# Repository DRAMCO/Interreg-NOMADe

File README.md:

# Interreg NOMADe
 Documentation about the Interreg NOMADe project

## Firmware
 This map contains the c/c++ code for both the DCU (Data Capturing Unit) and the motion sensor module
 
## Hardware
 Here you can find the Eagle schematics for the DCU and the sensor module

## Drawings
 Contains the 3D part files and STL files. 
 
 ## How to cite
```LaTex
@Misc{Interreg-NOMADe,
  author =   {J. Van Mulders},
  title =    {{Interreg-NOMADe}},
  howpublished  = "\url{https://github.com/DRAMCO/Interreg-NOMAD}",
  doi = {10.5281/zenodo.4005810}
}
```

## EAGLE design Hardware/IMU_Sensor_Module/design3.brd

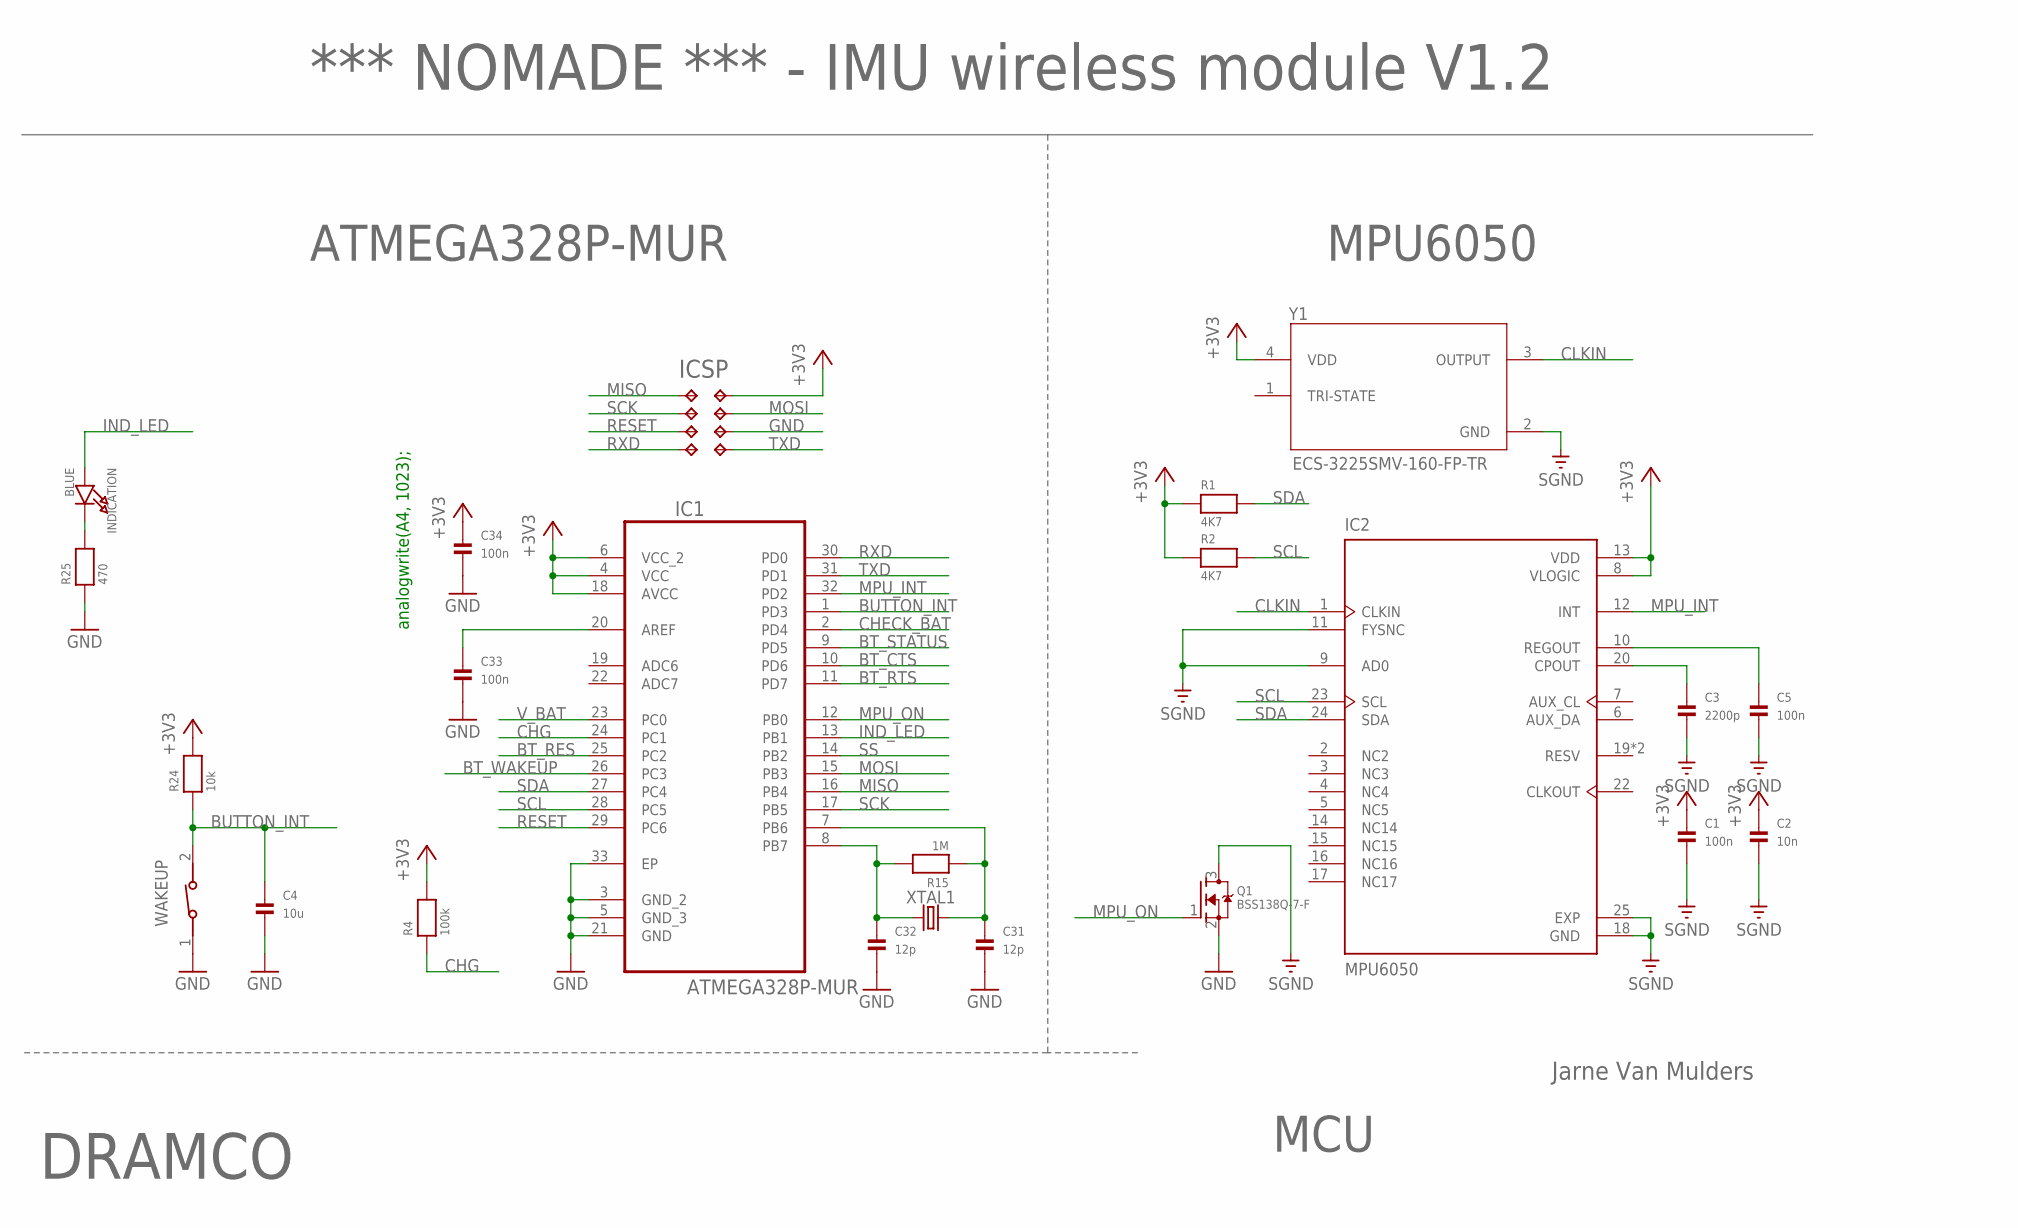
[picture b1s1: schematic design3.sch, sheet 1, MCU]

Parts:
3V3: TPTP16R; TP16R
C1, C5, C33, C34: 100n; 0603
C2: 10n; 0603
C3: 2200p; 0603
C4: 10u; 0805
C31, C32: 12p; 0603
GND: TPTP16R; TP16R
IC1: ATMEGA328P-MUR; QFN50P500X500X100-33N
IC2: MPU6050; IC_MPU6050
INDICATION: BLUE; CHIPLED_0805
MISO: TPTP16R; TP16R
MOSI: TPTP16R; TP16R
Q1: BSS138Q-7-F; SOT23-WIDE
R1, R2: 4K7; 0603
R4: 100k; 0603
R15: 1M; 0603
R24: 10k; 0603
R25: 470; 0603
RES: TPTP16R; TP16R
RXD: TPTP16R; TP16R
TP9: TPTP16R; TP16R
TXD: TPTP16R; TP16R
WAKEUP: 434111043826
XTAL1: CRYSTALSMD-3.2X2.5; CRYSTAL-SMD-3.2X2.5MM
Y1: ECS-3225SMV-160-FP-TR; OSC_ECS-2333-160-BN-TR

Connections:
+3V3: 3V3.TP, C1.1, C2.1, C34.1, IC1.4 (VCC), IC1.6 (VCC_2), IC1.18 (AVCC), IC2.8 (VLOGIC), IC2.13 (VDD), R1.1, R2.1, R4.2, R24.2, Y1.4 (VDD); also elsewhere on the board
BT_CTS: IC1.10 (PD6); also elsewhere on the board
BT_RES: IC1.25 (PC2); also elsewhere on the board
BT_RTS: IC1.11 (PD7); also elsewhere on the board
BT_STATUS: IC1.9 (PD5); also elsewhere on the board
BT_WAKEUP: IC1.26 (PC3); also elsewhere on the board
BUTTON_INT: C4.1, IC1.1 (PD3), R24.1, WAKEUP.2
CHECK_BAT: IC1.2 (PD4); also elsewhere on the board
CHG: IC1.24 (PC1), R4.1; also elsewhere on the board
CLKIN: IC2.1 (CLKIN), Y1.3 (OUTPUT)
GND: C4.2, C31.2, C32.2, C33.2, C34.2, GND.TP, IC1.3 (GND_2), IC1.5 (GND_3), IC1.21 (GND), IC1.33 (EP), Q1.2 (S), R25.1, WAKEUP.1; also elsewhere on the board
IND: INDICATION.C, R25.2
IND_LED: IC1.13 (PB1), INDICATION.A
MISO: IC1.16 (PB4), MISO.TP
MOSI: IC1.15 (PB3), MOSI.TP
MPU_INT: IC1.32 (PD2), IC2.12 (INT)
MPU_ON: IC1.12 (PB0), Q1.1 (G)
unnamed: C3.1, IC2.20 (CPOUT)
unnamed: C5.1, IC2.10 (REGOUT)
unnamed: C31.1, IC1.7 (PB6), R15.1, XTAL1.3 (2)
unnamed: C32.1, IC1.8 (PB7), R15.2, XTAL1.1
unnamed: C33.1, IC1.20 (AREF)
RESET: IC1.29 (PC6), RES.TP
RXD: IC1.30 (PD0), RXD.TP; also elsewhere on the board
SCK: IC1.17 (PB5), TP9.TP
SCL: IC1.28 (PC5), IC2.23 (SCL), R2.2
SDA: IC1.27 (PC4), IC2.24 (SDA), R1.2
SGND: C1.2, C2.2, C3.2, C5.2, IC2.9 (AD0), IC2.11 (FYSNC), IC2.18 (GND), IC2.25 (EXP), Q1.3 (D), Y1.2 (GND)
SS: IC1.14 (PB2)
TXD: IC1.31 (PD1), TXD.TP; also elsewhere on the board
V_BAT: IC1.23 (PC0); also elsewhere on the board

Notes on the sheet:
ATMEGA328P-MUR
*** NOMADE *** - IMU wireless module V1.2
MCU
Jarne Van Mulders
DRAMCO
ICSP
analogwrite(A4, 1023);
MPU6050

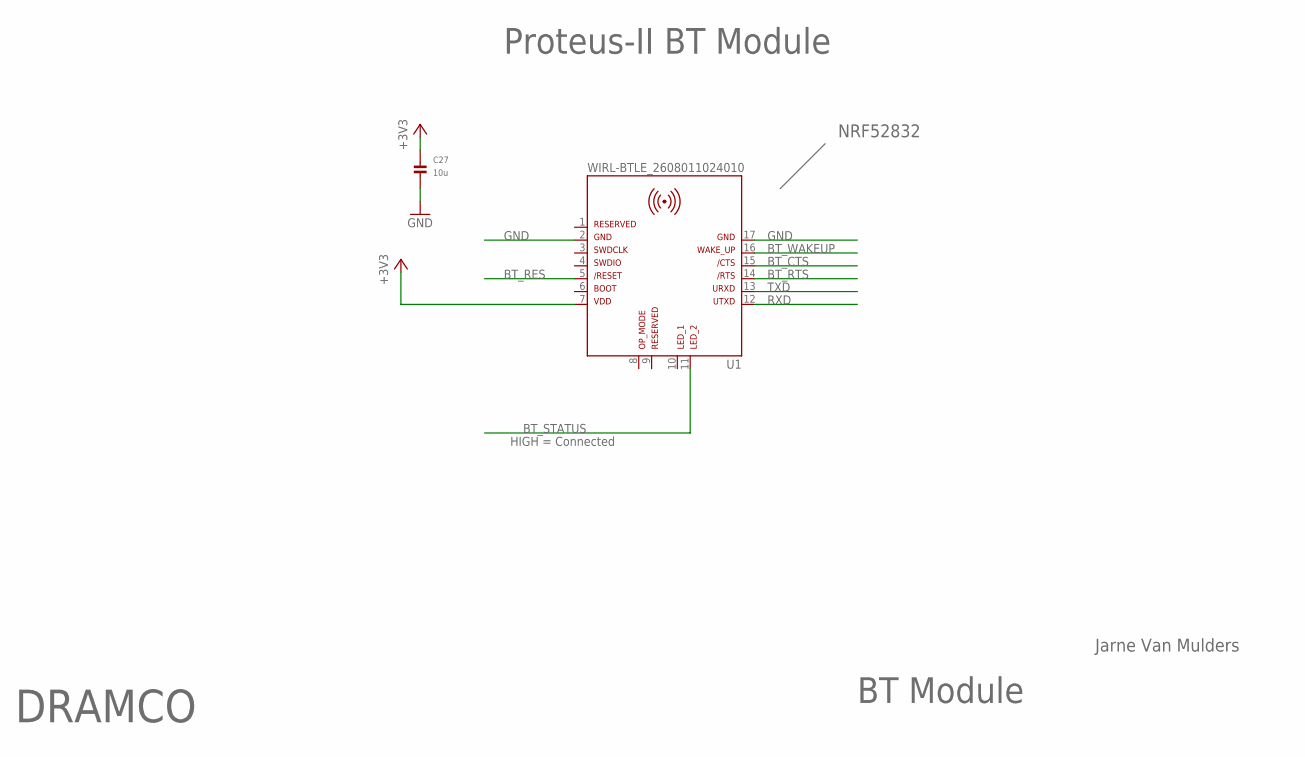
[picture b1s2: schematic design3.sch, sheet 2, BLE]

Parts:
C27: 10u; 0805
U1: WIRL-BTLE_2608011024010

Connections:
+3V3: C27.1, U1.7; also elsewhere on the board
BT_CTS: U1.15; also elsewhere on the board
BT_RES: U1.5; also elsewhere on the board
BT_RTS: U1.14; also elsewhere on the board
BT_STATUS: U1.11; also elsewhere on the board
BT_WAKEUP: U1.16; also elsewhere on the board
GND: C27.2, U1.2, U1.17; also elsewhere on the board
RXD: U1.12; also elsewhere on the board
TXD: U1.13; also elsewhere on the board

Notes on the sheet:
HIGH = Connected
BT Module
Jarne Van Mulders
DRAMCO
Proteus-II BT Module
NRF52832

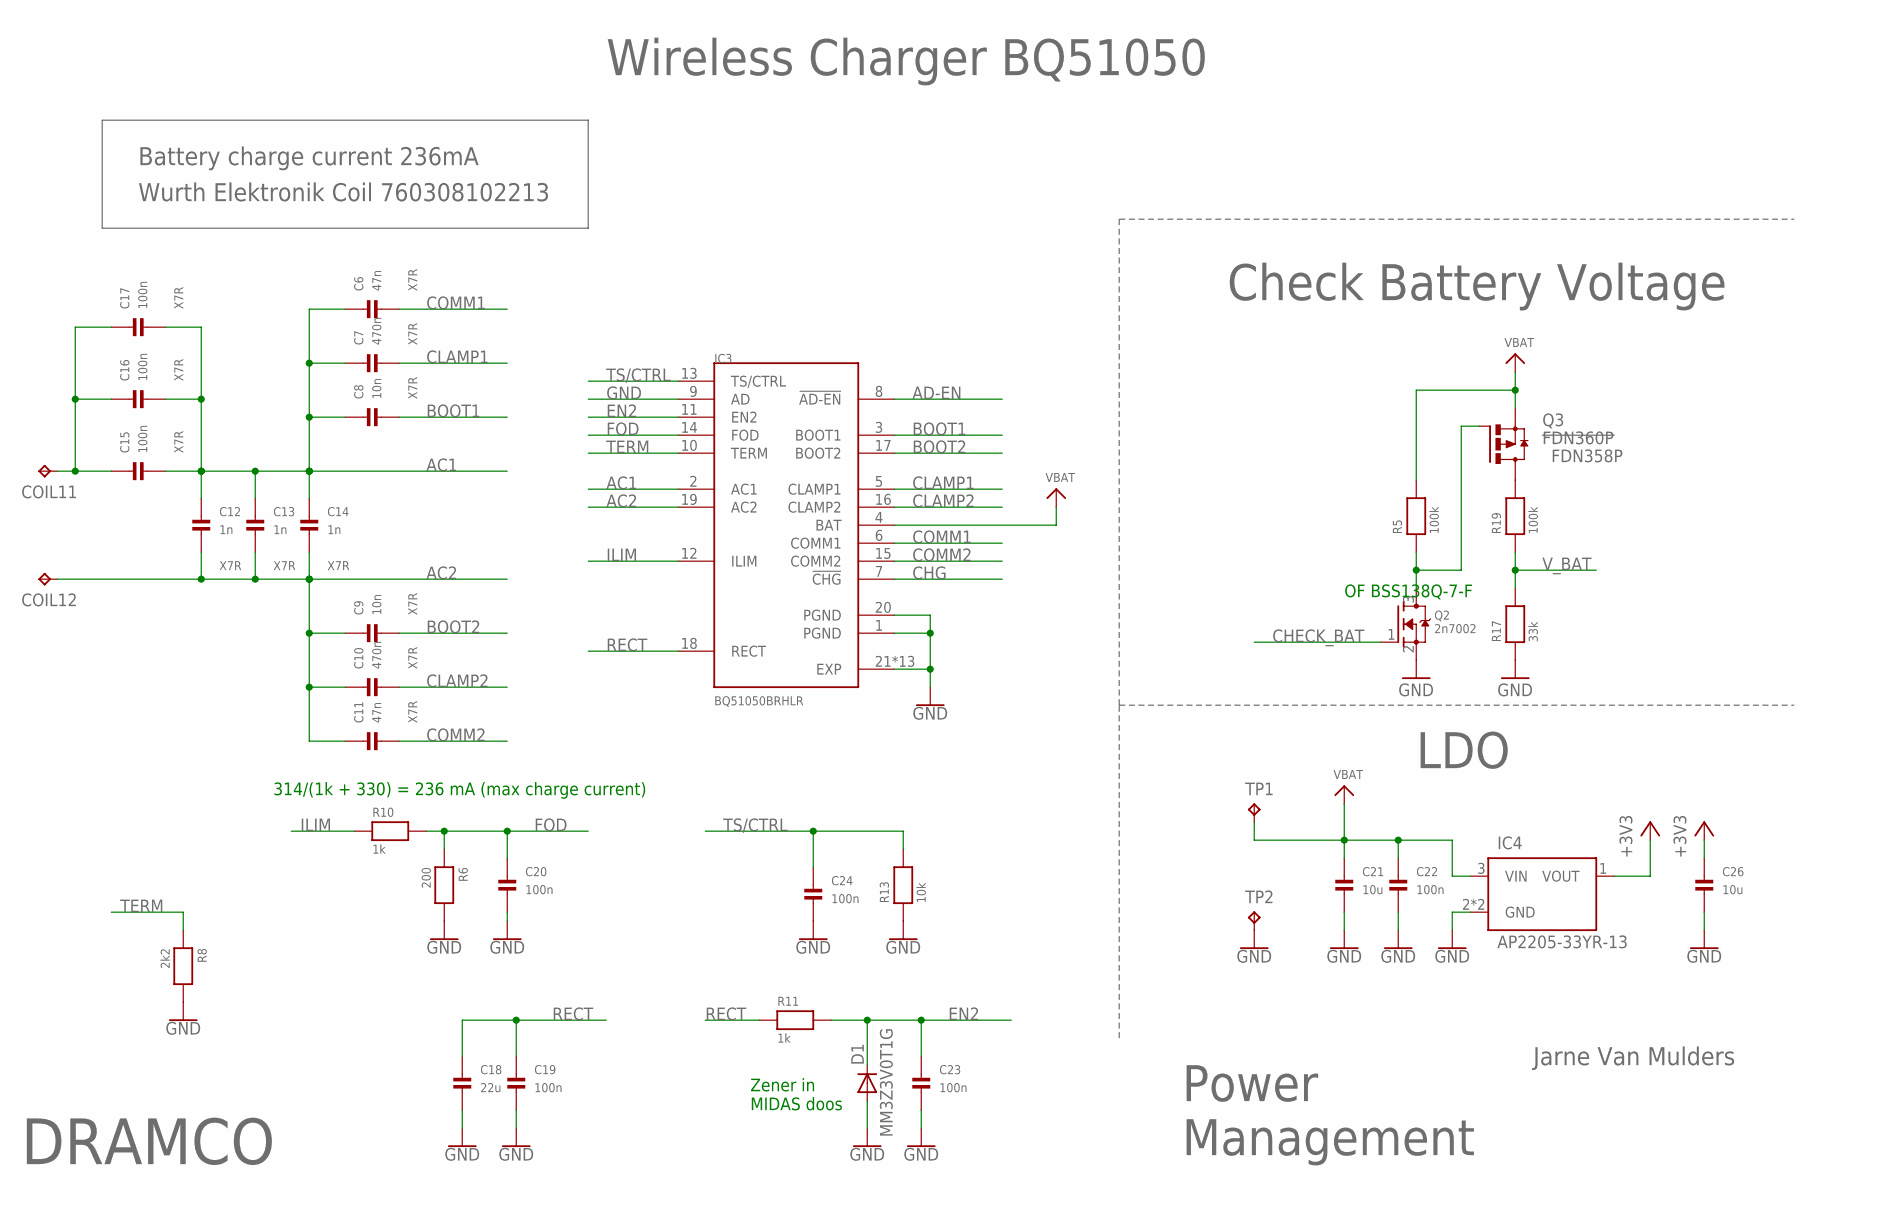
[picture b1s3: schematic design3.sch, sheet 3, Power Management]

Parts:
C6, C11: 47n; 0603
C7, C10: 470n; 0603
C8, C9: 10n; 0603
C12, C13, C14: 1n; 0805
C15, C16, C17: 100n; 0805
C18: 22u; 0805
C19, C20, C22, C23, C24: 100n; 0603
C21, C26: 10u; 0805
COIL11, COIL12: TPTP10SQ; TP10SQ
D1: MM3Z3V0T1G; SOD323-W
IC3: BQ51050BRHLR; QFN50P450X350X100-21N
IC4: AP2205-33YR-13; SOT150P410X160-3N
Q2: 2n7002; SOT23-WIDE
Q3: FDN360P; SUPER-SOT3
R5, R19: 100k; 0603
R6: 200; 0603
R8: 2k2; 0603
R10, R11: 1k; 0603
R13: 10k; 0603
R17: 33k; 0603
TP1, TP2: TPTP20SQ; TP20SQ

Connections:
+3V3: C26.1, IC4.1 (VOUT); also elsewhere on the board
AC1: C6.1, C7.1, C8.1, C12.1, C13.1, C14.1, C15.2, C16.2, C17.2, IC3.2 (AC1)
AC2: C9.1, C10.1, C11.1, C12.2, C13.2, C14.2, COIL12.TP, IC3.19 (AC2)
AC11: C15.1, C16.1, C17.1, COIL11.TP
AD-EN: IC3.8 (!AD-EN)
BOOT1: C8.2, IC3.3 (BOOT1)
BOOT2: C9.2, IC3.17 (BOOT2)
CHECK_BAT: Q2.1 (G); also elsewhere on the board
CHG: IC3.7 (!CHG); also elsewhere on the board
CLAMP1: C7.2, IC3.5 (CLAMP1)
CLAMP2: C10.2, IC3.16 (CLAMP2)
COMM1: C6.2, IC3.6 (COMM1)
COMM2: C11.2, IC3.15 (COMM2)
EN2: C23.1, D1.C, IC3.11 (EN2), R11.2
FOD: C20.1, IC3.14 (FOD), R6.1, R10.2
GND: C18.2, C19.2, C20.2, C21.2, C22.2, C23.2, C24.2, C26.2, D1.A, IC3.1 (PGND), IC3.9 (AD), IC3.20 (PGND), IC3.21 (EXP), IC3.22 (EXP), IC3.23 (EXP), IC3.24 (EXP), IC3.25 (EXP), IC3.26 (EXP), IC3.27 (EXP), IC3.28 (EXP), IC3.29 (EXP), IC3.30 (EXP), IC3.31 (EXP), IC3.32 (EXP), IC3.33 (EXP), IC4.2 (GND), IC4.4 (GND), Q2.2 (S), R6.2, R8.2, R13.1, R17.1, TP2.TP; also elsewhere on the board
ILIM: IC3.12 (ILIM), R10.1
unnamed: Q2.3 (D), Q3.1 (G), R5.1
unnamed: Q3.3 (D), R19.2
RECT: C18.1, C19.1, IC3.18 (RECT), R11.1
TERM: IC3.10 (TERM), R8.1
TS/CTRL: C24.1, IC3.13 (TS/CTRL), R13.2
VBAT: C21.1, C22.1, IC3.4 (BAT), IC4.3 (VIN), Q3.2 (S), R5.2, TP1.TP
V_BAT: R17.2, R19.1; also elsewhere on the board

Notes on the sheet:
Wurth Elektronik Coil 760308102213
Power Management
Jarne Van Mulders
DRAMCO
Zener in MIDAS doos
314/(1k + 330) = 236 mA (max charge current)
X7R
Battery charge current 236mA
Wireless Charger BQ51050
FDN358P
Check Battery Voltage
LDO
OF BSS138Q-7-F

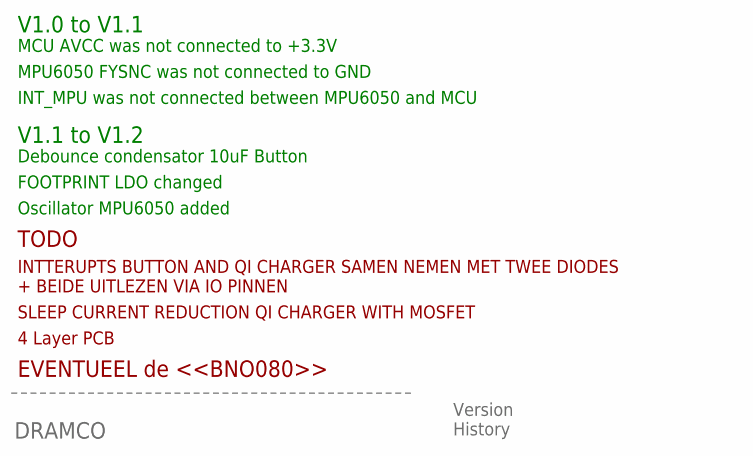
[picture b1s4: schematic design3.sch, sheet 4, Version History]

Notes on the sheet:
MCU AVCC was not connected to +3.3V
MPU6050 FYSNC was not connected to GND
INT_MPU was not connected between MPU6050 and MCU
Debounce condensator 10uF Button
FOOTPRINT LDO changed
INTTERUPTS BUTTON AND QI CHARGER SAMEN NEMEN MET TWEE DIODES + BEIDE UITLEZEN VIA IO PINNEN
SLEEP CURRENT REDUCTION QI CHARGER WITH MOSFET
V1.0 to V1.1
V1.1 to V1.2
Oscillator MPU6050 added
TODO
4 Layer PCB
EVENTUEEL de <<BNO080>>
DRAMCO
Version History

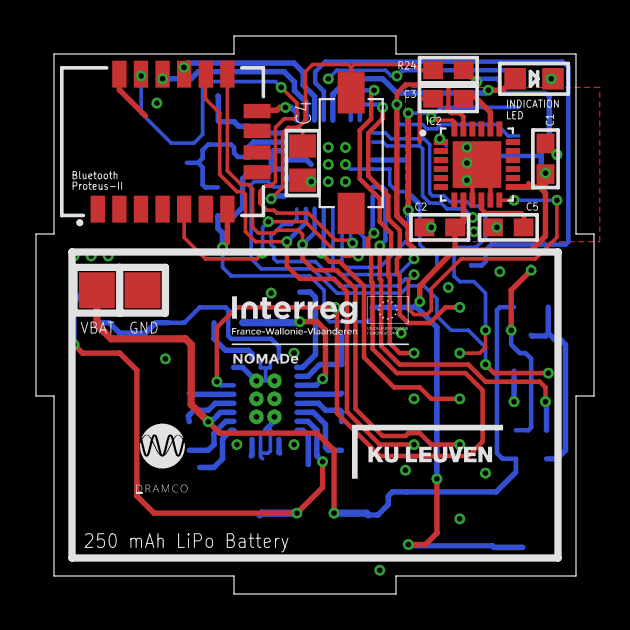
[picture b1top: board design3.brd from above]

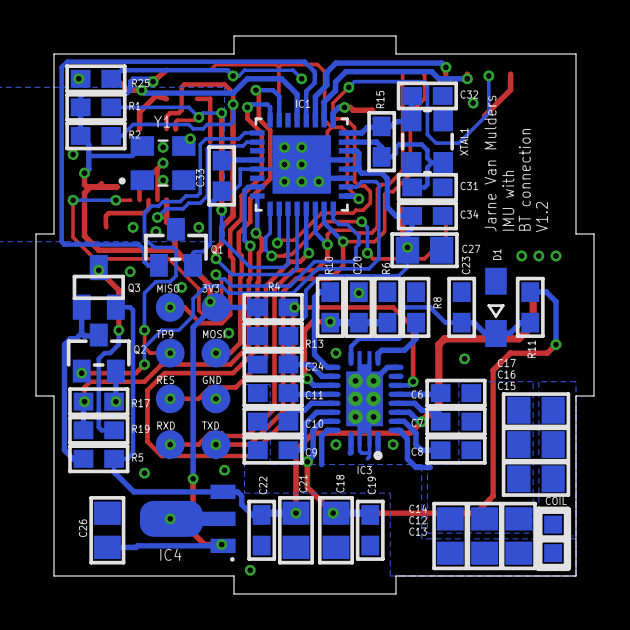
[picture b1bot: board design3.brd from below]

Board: 2 copper layers, 31.0 x 31.0 mm, 69 parts (57 on the bottom side), 48 nets.

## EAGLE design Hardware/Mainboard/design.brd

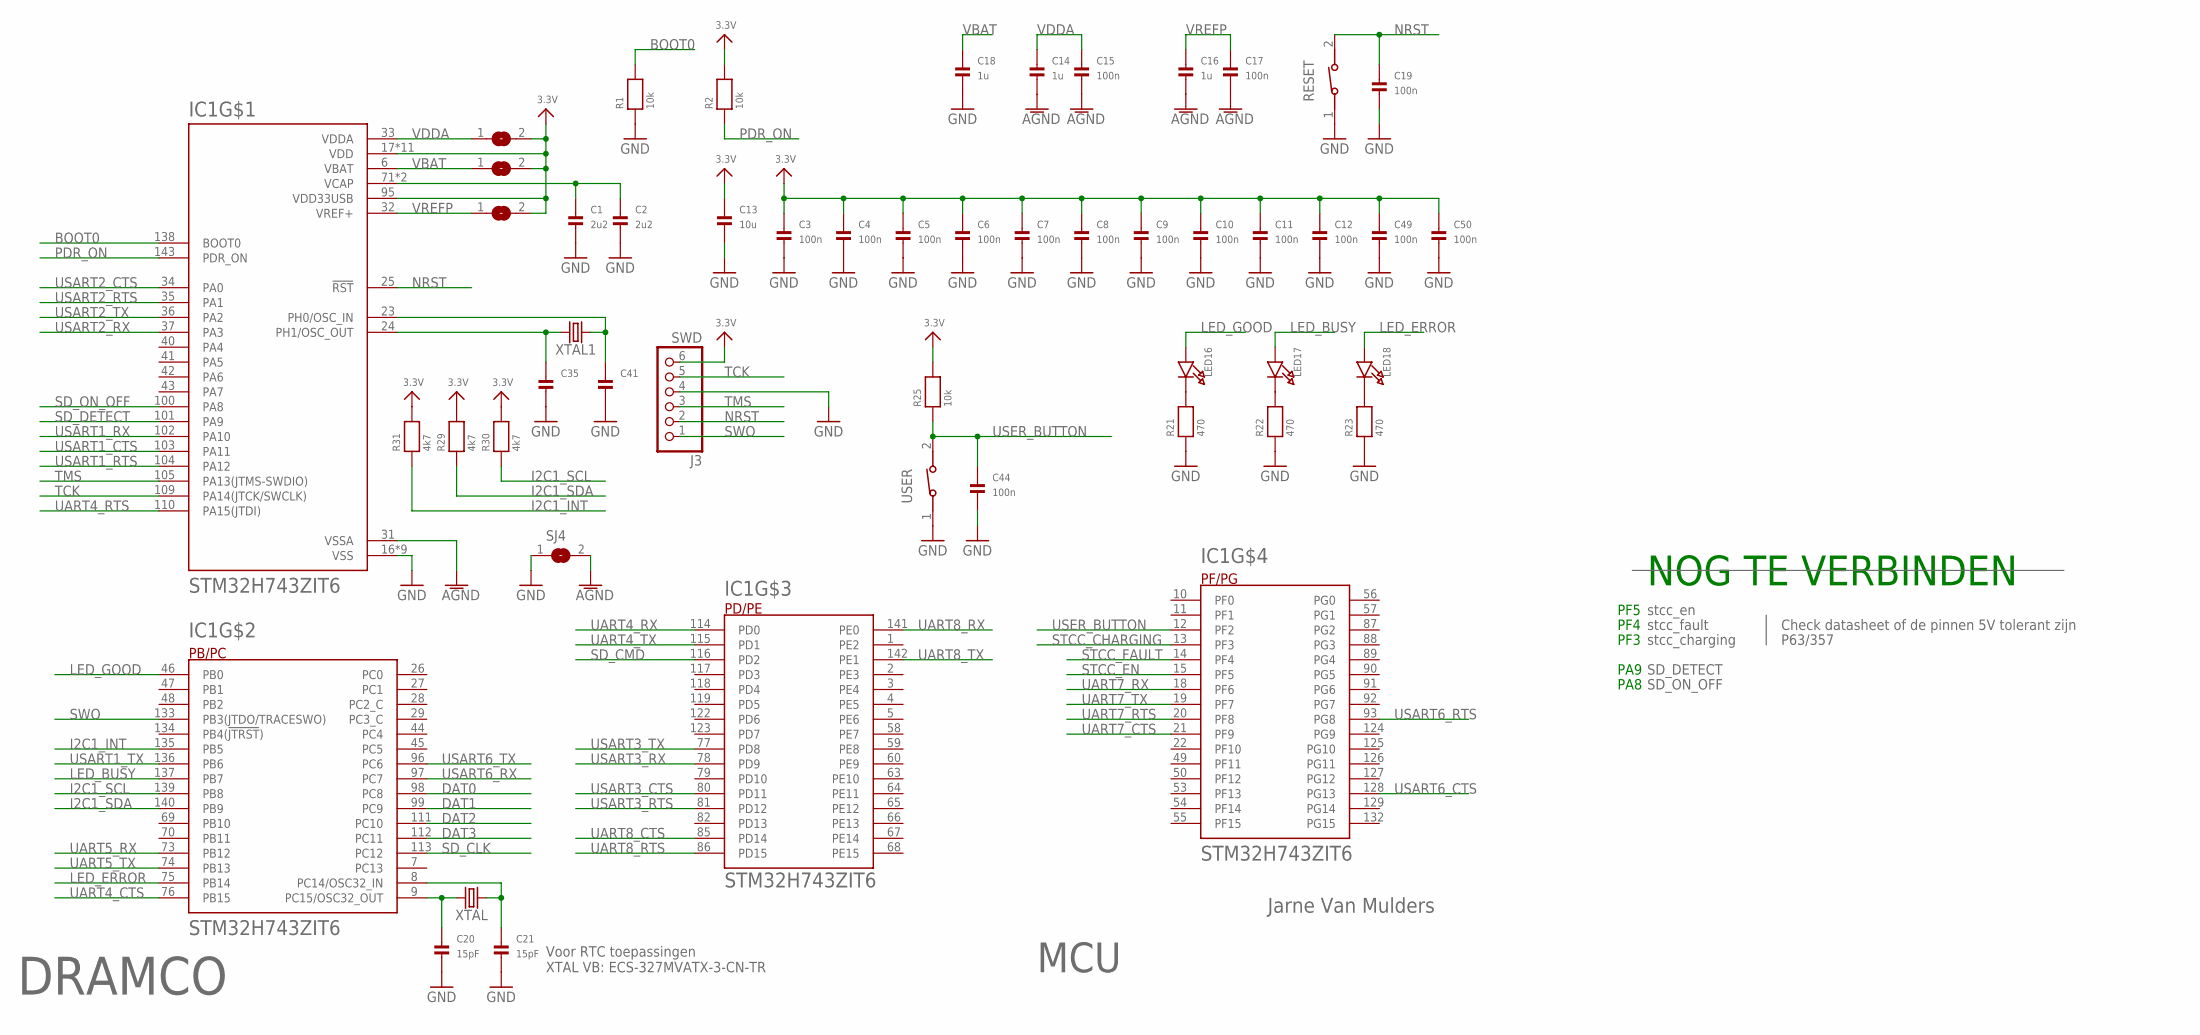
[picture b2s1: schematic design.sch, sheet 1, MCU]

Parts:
C1, C2: 2u2; 0805
C3, C4, C5, C6, C7, C8, C9, C10, C11, C12, C15, C17, C19, C44, C49, C50: 100n; 0603
C13: 10u; 0805
C14, C16, C18: 1u; 0603
C20, C21: 15pF; 0603
C35, C41: CAP_CERAMIC0603; 0603
IC1: STM32H743ZIT6; QFP50P2200X2200X160-144N
J3: SWD; 1X06_ROUND
LED16, LED17, LED18: LED0805; CHIPLED_0805
R1, R2, R25: 10k; 0603
R21, R22, R23: 470; 0603
R29, R30, R31: 4k7; 0603
RESET: 434111043826
SJ1, SJ2, SJ3, SJ4: SOLDERJUMPERCLOSED; SOLDERJUMPER_CLOSEDWIRE
USER: 434111043826
XTAL, XTAL1: CRYSTALSMD-3.2X2.5; CRYSTAL-SMD-3.2X2.5MM

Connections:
3.3V: C3.1, C4.1, C5.1, C6.1, C7.1, C8.1, C9.1, C10.1, C11.1, C12.1, C13.1, C49.1, C50.1, IC1.17 (VDD), IC1.30 (VDD), IC1.39 (VDD), IC1.52 (VDD), IC1.62 (VDD), IC1.72 (VDD), IC1.84 (VDD), IC1.95 (VDD33USB), IC1.108 (VDD), IC1.121 (VDD), IC1.131 (VDD), IC1.144 (VDD), J3.6, R2.2, R25.2, R29.2, R30.2, R31.2, SJ1.2, SJ2.2, SJ3.2; also elsewhere on the board
AGND: C14.2, C15.2, C16.2, C17.2, IC1.31 (VSSA), SJ4.2
BOOT0: IC1.138 (BOOT0), R1.2
DAT0: IC1.98 (PC8); also elsewhere on the board
DAT1: IC1.99 (PC9); also elsewhere on the board
DAT2: IC1.111 (PC10); also elsewhere on the board
DAT3: IC1.112 (PC11); also elsewhere on the board
GND: C1.2, C2.2, C3.2, C4.2, C5.2, C6.2, C7.2, C8.2, C9.2, C10.2, C11.2, C12.2, C13.2, C18.2, C19.2, C20.2, C21.2, C35.2, C41.2, C44.2, C49.2, C50.2, IC1.16 (VSS), IC1.38 (VSS), IC1.51 (VSS), IC1.61 (VSS), IC1.83 (VSS), IC1.94 (VSS), IC1.107 (VSS), IC1.120 (VSS), IC1.130 (VSS), J3.4, R1.1, R21.1, R22.1, R23.1, RESET.1, SJ4.1, USER.1; also elsewhere on the board
I2C1_INT: IC1.135 (PB5), R31.1; also elsewhere on the board
I2C1_SCL: IC1.139 (PB8), R30.1; also elsewhere on the board
I2C1_SDA: IC1.140 (PB9), R29.1; also elsewhere on the board
LED_BUSY: IC1.137 (PB7), LED17.A
LED_ERROR: IC1.75 (PB14), LED18.A
LED_GOOD: IC1.46 (PB0), LED16.A
unnamed: C1.1, C2.1, IC1.71 (VCAP), IC1.106 (VCAP)
unnamed: C20.1, IC1.9 (PC15/OSC32_OUT), XTAL.3 (2)
unnamed: C21.1, IC1.8 (PC14/OSC32_IN), XTAL.1
unnamed: LED16.C, R21.2
unnamed: LED17.C, R22.2
unnamed: C35.1, IC1.24 (PH1/OSC_OUT), XTAL1.3 (2)
unnamed: LED18.C, R23.2
unnamed: C41.1, IC1.23 (PH0/OSC_IN), XTAL1.1
NRST: C19.1, IC1.25 (!RST), J3.2, RESET.2
PDR_ON: IC1.143 (PDR_ON), R2.1
SD_CLK: IC1.113 (PC12); also elsewhere on the board
SD_CMD: IC1.116 (PD2); also elsewhere on the board
SD_DETECT: IC1.101 (PA9); also elsewhere on the board
SD_ON_OFF: IC1.100 (PA8); also elsewhere on the board
STCC_CHARGING: IC1.13 (PF3); also elsewhere on the board
STCC_EN: IC1.15 (PF5); also elsewhere on the board
STCC_FAULT: IC1.14 (PF4); also elsewhere on the board
SWO: IC1.133 (PB3(JTDO/TRACESWO)), J3.1
TCK: IC1.109 (PA14(JTCK/SWCLK)), J3.5
TMS: IC1.105 (PA13(JTMS-SWDIO)), J3.3
UART4_CTS: IC1.76 (PB15); also elsewhere on the board
UART4_RTS: IC1.110 (PA15(JTDI)); also elsewhere on the board
UART4_RX: IC1.114 (PD0); also elsewhere on the board
UART4_TX: IC1.115 (PD1); also elsewhere on the board
UART5_RX: IC1.73 (PB12); also elsewhere on the board
UART5_TX: IC1.74 (PB13); also elsewhere on the board
UART7_CTS: IC1.21 (PF9); also elsewhere on the board
UART7_RTS: IC1.20 (PF8); also elsewhere on the board
UART7_RX: IC1.18 (PF6); also elsewhere on the board
UART7_TX: IC1.19 (PF7); also elsewhere on the board
UART8_CTS: IC1.85 (PD14); also elsewhere on the board
UART8_RTS: IC1.86 (PD15); also elsewhere on the board
UART8_RX: IC1.141 (PE0); also elsewhere on the board
UART8_TX: IC1.142 (PE1); also elsewhere on the board
USART1_CTS: IC1.103 (PA11); also elsewhere on the board
USART1_RTS: IC1.104 (PA12); also elsewhere on the board
USART1_RX: IC1.102 (PA10); also elsewhere on the board
USART1_TX: IC1.136 (PB6); also elsewhere on the board
USART2_CTS: IC1.34 (PA0); also elsewhere on the board
USART2_RTS: IC1.35 (PA1); also elsewhere on the board
USART2_RX: IC1.37 (PA3); also elsewhere on the board
USART2_TX: IC1.36 (PA2); also elsewhere on the board
USART3_CTS: IC1.80 (PD11); also elsewhere on the board
USART3_RTS: IC1.81 (PD12); also elsewhere on the board
USART3_RX: IC1.78 (PD9); also elsewhere on the board
USART3_TX: IC1.77 (PD8); also elsewhere on the board
USART6_CTS: IC1.128 (PG13); also elsewhere on the board
USART6_RTS: IC1.93 (PG8); also elsewhere on the board
USART6_RX: IC1.97 (PC7); also elsewhere on the board
USART6_TX: IC1.96 (PC6); also elsewhere on the board
USER_BUTTON: C44.1, IC1.12 (PF2), R25.1, USER.2
VBAT: C18.1, IC1.6 (VBAT), SJ2.1
VDDA: C14.1, C15.1, IC1.33 (VDDA), SJ3.1
VREFP: C16.1, C17.1, IC1.32 (VREF+), SJ1.1

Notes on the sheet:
Voor RTC toepassingen XTAL VB: ECS-327MVATX-3-CN-TR
MCU
Jarne Van Mulders
DRAMCO
NOG TE VERBINDEN
stcc_en
stcc_fault
stcc_charging
Check datasheet of de pinnen 5V tolerant zijn
P63/357
SD_DETECT
SD_ON_OFF
PA9
PA8
PF3
PF4
PF5

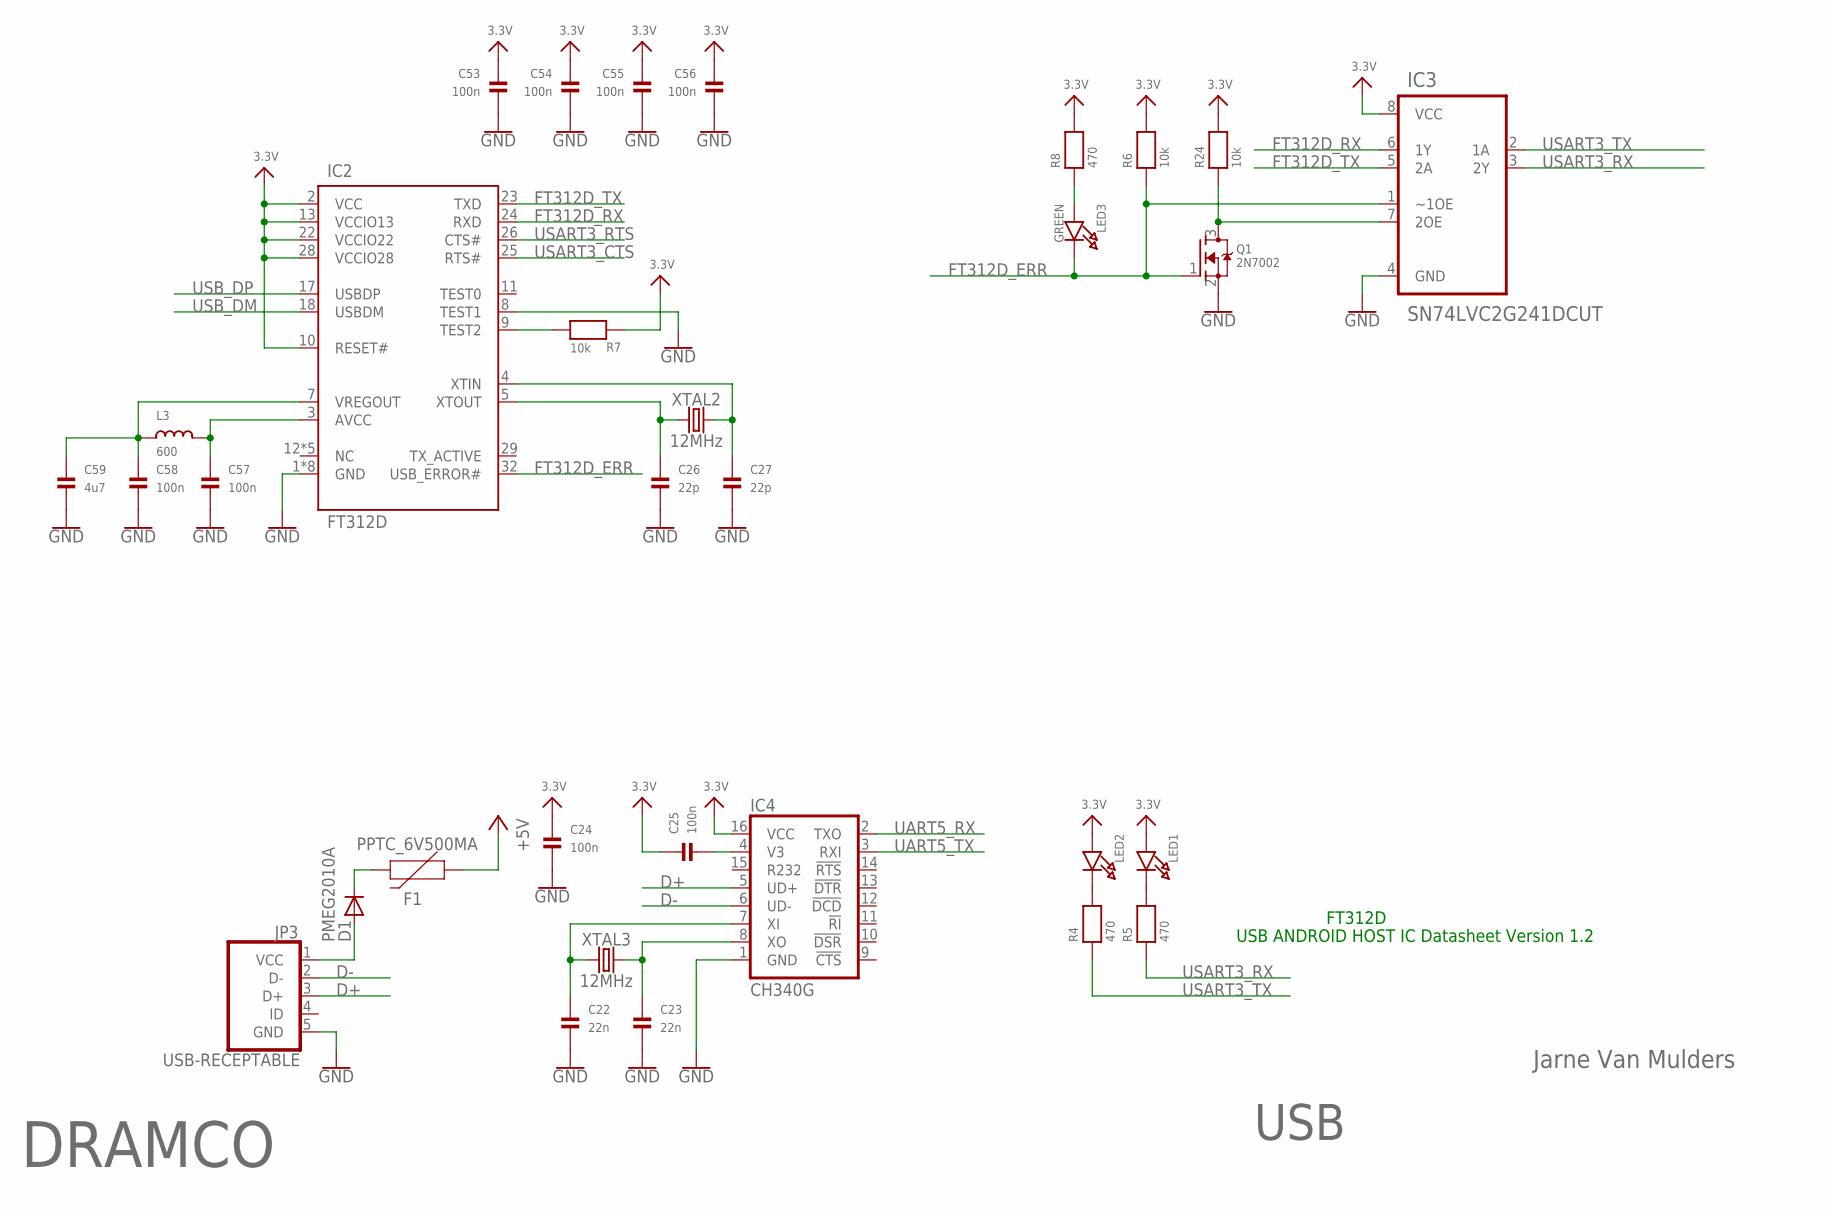
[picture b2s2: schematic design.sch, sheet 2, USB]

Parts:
C22, C23: 22n; 0603
C24, C25, C53, C54, C55, C56, C57, C58: 100n; 0603
C26, C27: 22p; 0603
C59: 4u7; 0603
D1: PMEG2010A; SOD323-W
F1: PPTC_6V500MA; 0805
IC2: FT312D; QFP80P900X900X160-32N
IC3: SN74LVC2G241DCUT; SOP50P310X90-8N
IC4: CH340G; SO016
JP3: USB-RECEPTABLE; FCI-10103594-0001LF
L3: 600; 0603
LED1, LED2: LED0805; CHIPLED_0805
LED3: GREEN; CHIPLED_0805
Q1: 2N7002; SOT23-WIDE
R4, R5, R8: 470; 0603
R6, R7, R24: 10k; 0603
XTAL2, XTAL3: 12MHz; CRYSTAL-SMD-3.2X2.5MM

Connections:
3.3V: C24.1, C25.1, C53.1, C54.1, C55.1, C56.1, IC2.2 (VCC), IC2.10 (RESET#), IC2.13 (VCCIO13), IC2.22 (VCCIO22), IC2.28 (VCCIO28), IC3.8 (VCC), IC4.16 (VCC), LED1.A, LED2.A, R6.2, R7.2, R8.2, R24.2; also elsewhere on the board
+5V: F1.1; also elsewhere on the board
D+: IC4.5 (UD+), JP3.3 (D+)
D-: IC4.6 (UD-), JP3.2 (D-)
FT312D_ERR: IC2.32 (USB_ERROR#), IC3.1 (~1OE), LED3.C, Q1.1 (G), R6.1
FT312D_RX: IC2.24 (RXD), IC3.6 (1Y)
FT312D_TX: IC2.23 (TXD), IC3.5 (2A)
GND: C22.2, C23.2, C24.2, C26.2, C27.2, C53.2, C54.2, C55.2, C56.2, C57.2, C58.2, C59.2, IC2.1 (GND), IC2.6 (GND), IC2.8 (TEST1), IC2.14 (GND), IC2.15 (GND), IC2.16 (GND), IC2.19 (GND), IC2.27 (GND), IC2.33 (GND), IC3.4 (GND), IC4.1 (GND), JP3.5 (GND), Q1.2 (S); also elsewhere on the board
unnamed: LED2.C, R4.2
unnamed: LED1.C, R5.2
unnamed: C27.1, IC2.4 (XTIN), XTAL2.3 (2)
unnamed: C26.1, IC2.5 (XTOUT), XTAL2.1
unnamed: D1.C, F1.2
unnamed: LED3.A, R8.1
unnamed: IC2.9 (TEST2), R7.1
unnamed: IC3.7 (2OE), Q1.3 (D), R24.1
unnamed: D1.A, JP3.1 (VCC)
unnamed: C22.1, IC4.7 (XI), XTAL3.1
unnamed: C23.1, IC4.8 (XO), XTAL3.3 (2)
unnamed: C25.2, IC4.4 (V3)
unnamed: C58.1, C59.1, IC2.7 (VREGOUT), L3.1
unnamed: C57.1, IC2.3 (AVCC), L3.2
UART5_RX: IC4.2 (TXO); also elsewhere on the board
UART5_TX: IC4.3 (RXI); also elsewhere on the board
USART3_CTS: IC2.25 (RTS#); also elsewhere on the board
USART3_RTS: IC2.26 (CTS#); also elsewhere on the board
USART3_RX: IC3.3 (2Y), R5.1; also elsewhere on the board
USART3_TX: IC3.2 (1A), R4.1; also elsewhere on the board
USB_DM: IC2.18 (USBDM); also elsewhere on the board
USB_DP: IC2.17 (USBDP); also elsewhere on the board

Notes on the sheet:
FT312D
USB ANDROID HOST IC Datasheet Version 1.2
USB
Jarne Van Mulders
DRAMCO

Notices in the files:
Firmware/IMU_Sensor_Module/ARCHIEF/main_archief.cpp:
I2Cdev device library code is placed under the MIT license
Copyright (c) 2012 Jeff Rowberg
parts and their libraries:
microbuilder: This work is placed in the public domain, and may be freely used for commercial and non-commercial work with the following conditions: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
Eagle_SWITCHES: Copyright: Würth Elektronik
supply0: Copyright (C) 2007, Bob Starr
